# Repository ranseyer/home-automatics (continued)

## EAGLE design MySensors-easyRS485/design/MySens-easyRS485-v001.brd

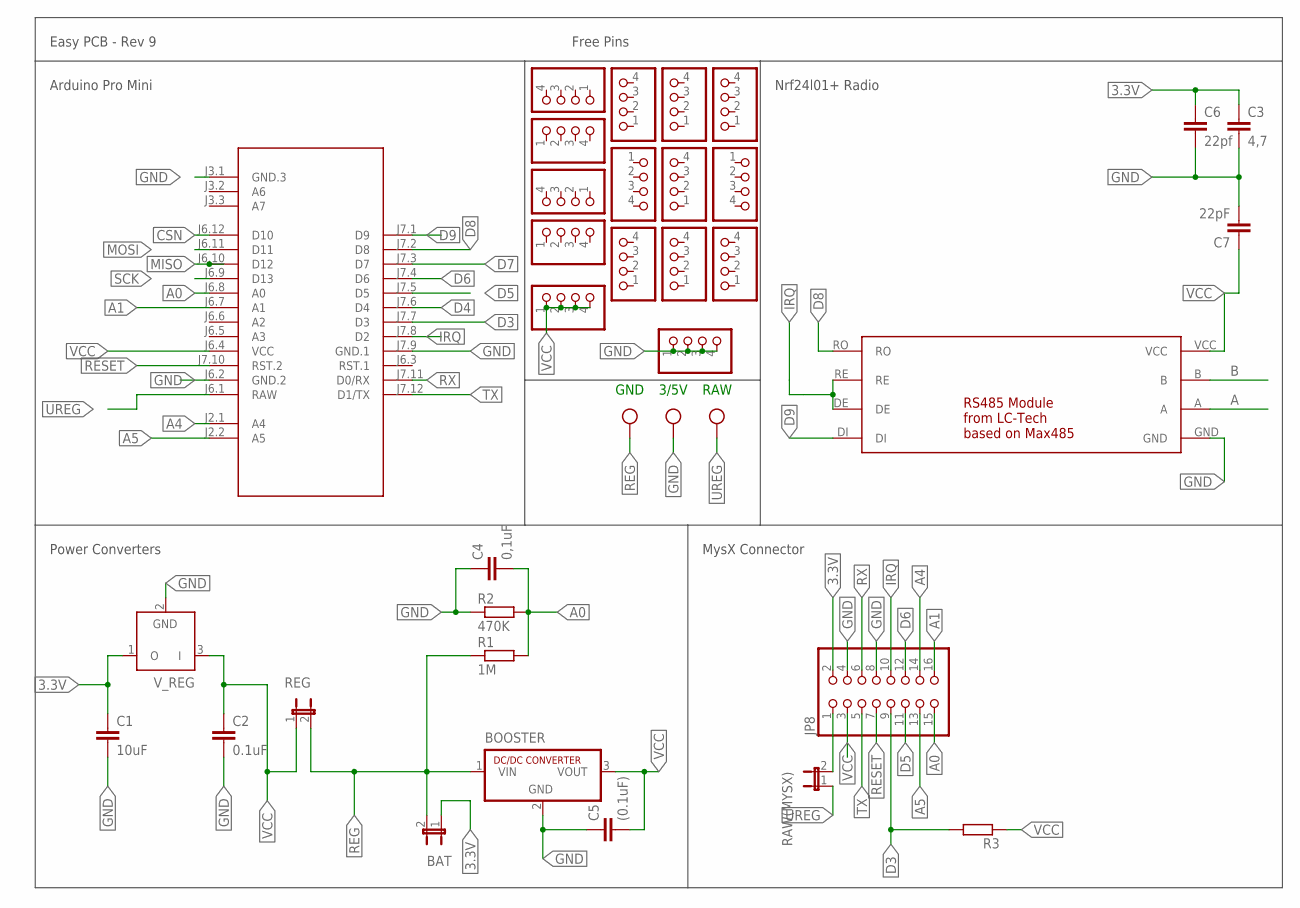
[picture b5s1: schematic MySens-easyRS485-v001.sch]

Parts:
.: W237-103
BAT: JP1E; JP1
BOOSTER: R-78C1.8-1.0; SIP3
C1: 10uF; C5B2.5
C2: 0.1uF; C5B2.5
C3: 4,7; C5B2.5
C4: 0,1uF; C5B2.5
C5: (0.1uF); C5B2.5
C6: 22pf; C0805
C7: 22pF; C0805
JP1, JP2, JP3, JP4, JP5, JP6, JP7, JP9, JP10, JP11, JP12, JP13, JP14, JP15, JP16: PINHD-1X04_2.54-S; 1X04-S
JP8: PINHD-2X08_2.54; 2X08
M1: ARDUINO-PRO-MINI-3.3V#NP; ARDUINO-PRO-MINI#NP
R1: 1M; 0204/7
R2: 470K; 0204/7
R3: R-EU_0204/7; 0204/7
RAW(MYSX): JP1E; JP1
REG: JP1E; JP1
U$1: RS485-LCTECH
V_REG: LP2950Z; TO92

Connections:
3.3V: BAT.1, C1.1, C3.1, C6.1, JP8.2, V_REG.1 (O)
A: U$1.A
A0: C4.2, JP8.15, M1.J6.8 (A0), R1.2, R2.2
A1: JP8.16, M1.J6.7 (A1)
A4: JP8.14, M1.J2.1 (A4)
A5: JP8.13, M1.J2.2 (A5)
B: U$1.B
CSN: M1.J6.12 (D10)
D3: JP8.9, M1.J7.7 (D3), R3.2
D4: M1.J7.6 (D4)
D5: JP8.11, M1.J7.5 (D5)
D6: JP8.12, M1.J7.4 (D6)
D7: M1.J7.3 (D7)
D8: M1.J7.2 (D8), U$1.RO
D9: M1.J7.1 (D9), U$1.DI
GND: ..2, BOOSTER.2 (GND), C1.2, C2.2, C3.2, C4.1, C5.1, C6.2, C7.2, JP1.1, JP1.2, JP1.3, JP1.4, JP8.4, JP8.8, M1.J3.1 (GND.3), M1.J6.2 (GND.2), M1.J7.9 (GND.1), R2.1, U$1.GND, V_REG.2 (GND)
IRQ: JP8.10, M1.J7.8 (D2), U$1.DE, U$1.RE
MISO: M1.J6.10 (D12)
MOSI: M1.J6.11 (D11)
unnamed: JP8.1, RAW(MYSX).2
REG: ..3, BAT.2, BOOSTER.1 (VIN), R1.1, REG.2
RESET: JP8.7, M1.J7.10 (RST.2)
RX: JP8.6, M1.J7.11 (D0/RX)
SCK: M1.J6.9 (D13)
TX: JP8.5, M1.J7.12 (D1/TX)
UREG: ..1, M1.J6.1 (RAW), RAW(MYSX).1
VCC: BOOSTER.3 (VOUT), C2.1, C5.2, C7.1, JP3.1, JP3.2, JP3.3, JP3.4, JP8.3, M1.J6.4 (VCC), R3.1, REG.1, U$1.VCC, V_REG.3 (I)

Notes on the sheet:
GND
3/5V
RAW
Easy PCB - Rev 9
Arduino Pro Mini
MysX Connector
Nrf24l01+ Radio
Power Converters
Free Pins

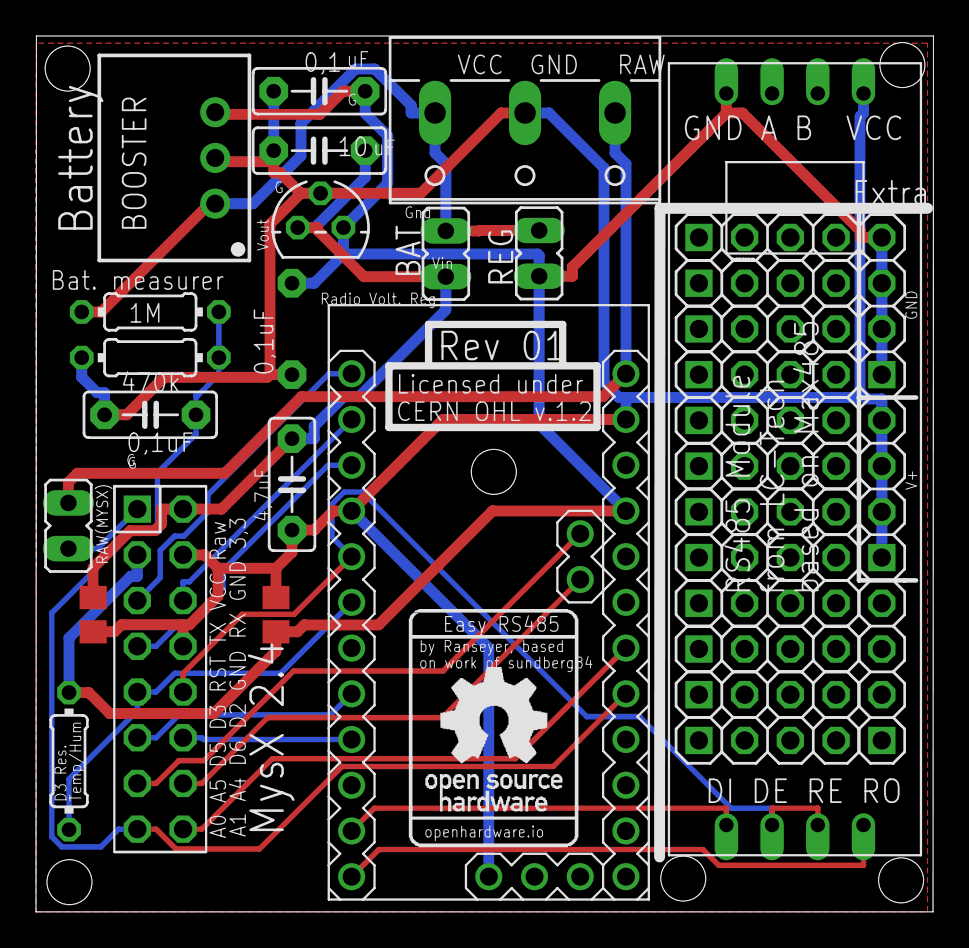
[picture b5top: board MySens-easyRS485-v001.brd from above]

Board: 2 copper layers, 49.9 x 48.7 mm, 34 parts (1 on the bottom side), 19 nets.
